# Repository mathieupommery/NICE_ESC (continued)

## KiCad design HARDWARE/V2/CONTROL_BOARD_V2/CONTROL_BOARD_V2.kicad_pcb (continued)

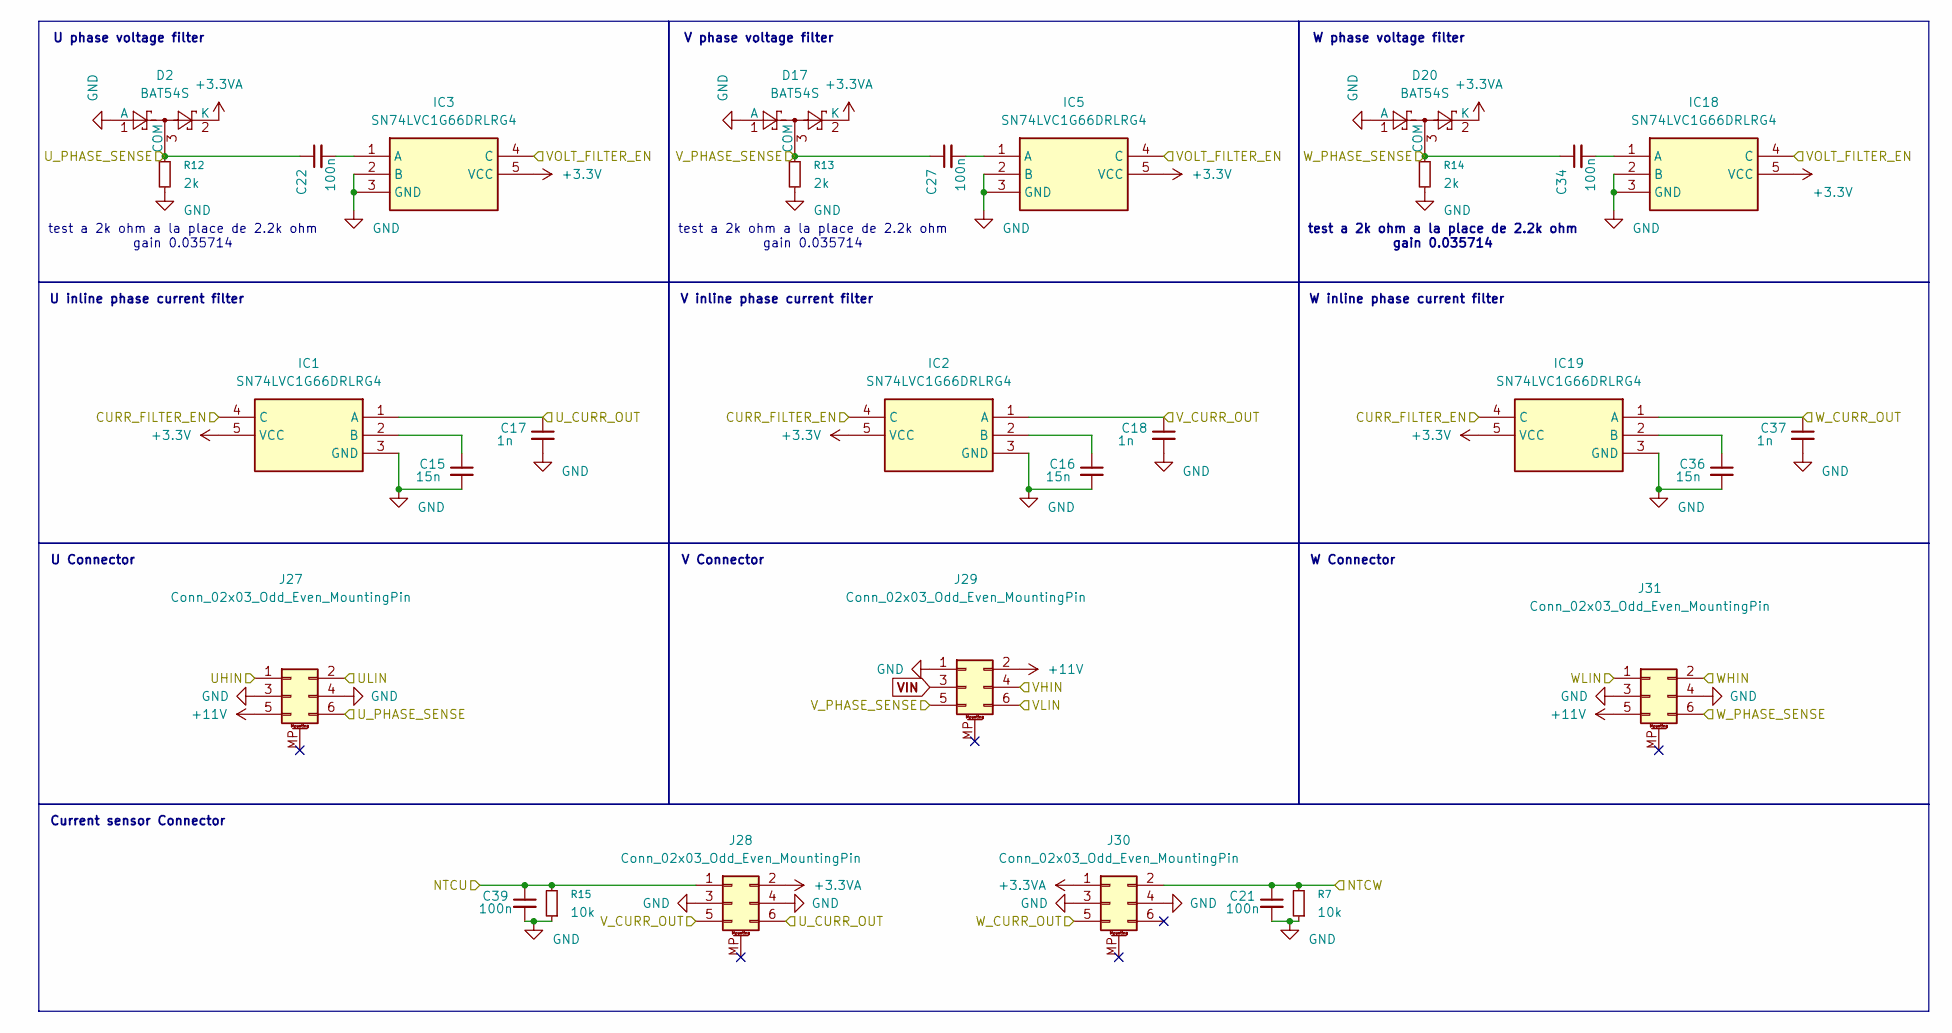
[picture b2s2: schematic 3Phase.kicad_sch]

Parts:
C15, C16, C36: 15n; C_0402_1005Metric
C17, C18, C37: 1n; C_0402_1005Metric
C21, C22, C27, C34, C39: 100n; C_0402_1005Metric
D2, D17, D20: BAT54S; SOT-23
IC1, IC2, IC3, IC5, IC18, IC19: SN74LVC1G66DRLRG4; SOTFL50P160X60-5N; Manufacturer_Part_Number SN74LVC1G66DRLRG4; Mouser Part Number 595-SN74LVC1G66DRG4
J27, J28, J29, J30, J31: Conn_02x03_Odd_Even_MountingPin; 2x3_pinheader
R7, R15: 10k; R_0402_1005Metric
R12, R13, R14: 2k; R_0402_1005Metric

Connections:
+3.3V: IC1.5 (VCC), IC2.5 (VCC), IC3.5 (VCC), IC5.5 (VCC), IC18.5 (VCC), IC19.5 (VCC); also elsewhere on the board
+3.3VA: D2.2 (K), D17.2 (K), D20.2 (K), J28.2, J30.1; also elsewhere on the board
+11V: J27.5, J29.2, J31.5; also elsewhere on the board
/3Phase_Conn_Filtering/UHIN: J27.1; also elsewhere on the board
/3Phase_Conn_Filtering/ULIN: J27.2; also elsewhere on the board
/3Phase_Conn_Filtering/VHIN: J29.4; also elsewhere on the board
/3Phase_Conn_Filtering/VLIN: J29.6; also elsewhere on the board
/3Phase_Conn_Filtering/WHIN: J31.2; also elsewhere on the board
/3Phase_Conn_Filtering/WLIN: J31.1; also elsewhere on the board
/ADC1_IN1: C17.1, IC1.1 (A), J28.6; also elsewhere on the board
/ADC1_IN2: C18.1, IC2.1 (A), J28.5; also elsewhere on the board
/ADC1_IN3: C37.1, IC19.1 (A), J30.5; also elsewhere on the board
/ADC1_IN11: C39.1, J28.1, R15.2; also elsewhere on the board
/ADC1_IN12: C21.1, J30.2, R7.2; also elsewhere on the board
/ADC2_IN3: C22.1, D2.3 (COM), J27.6, R12.1; also elsewhere on the board
/ADC2_IN4: C27.1, D17.3 (COM), J29.5, R13.1; also elsewhere on the board
/ADC2_IN5: C34.1, D20.3 (COM), J31.6, R14.1; also elsewhere on the board
/CURR_FILTER_EN: IC1.4 (C), IC2.4 (C), IC19.4 (C); also elsewhere on the board
/VOLT_FILTER_EN: IC3.4 (C), IC5.4 (C), IC18.4 (C); also elsewhere on the board
GND: C15.2, C16.2, C17.2, C18.2, C21.2, C36.2, C37.2, C39.2, D2.1 (A), D17.1 (A), D20.1 (A), IC1.3 (GND), IC2.3 (GND), IC3.2 (B), IC3.3 (GND), IC5.2 (B), IC5.3 (GND), IC18.2 (B), IC18.3 (GND), IC19.3 (GND), J27.3, J27.4, J28.3, J28.4, J29.1, J30.3, J30.4, J31.3, J31.4, R7.1, R12.2, R13.2, R14.2, R15.1; also elsewhere on the board
unnamed: C15.1, IC1.2 (B)
unnamed: C16.1, IC2.2 (B)
unnamed: C22.2, IC3.1 (A)
unnamed: C27.2, IC5.1 (A)
unnamed: C34.2, IC18.1 (A)
unnamed: C36.1, IC19.2 (B)
VIN: J29.3; also elsewhere on the board

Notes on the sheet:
W phase voltage filter
test a 2k ohm a la place de 2.2k ohm gain 0.035714
U Connector
U phase voltage filter
W inline phase current filter
W Connector
Current sensor Connector
V phase voltage filter
U inline phase current filter
V Connector
V inline phase current filter

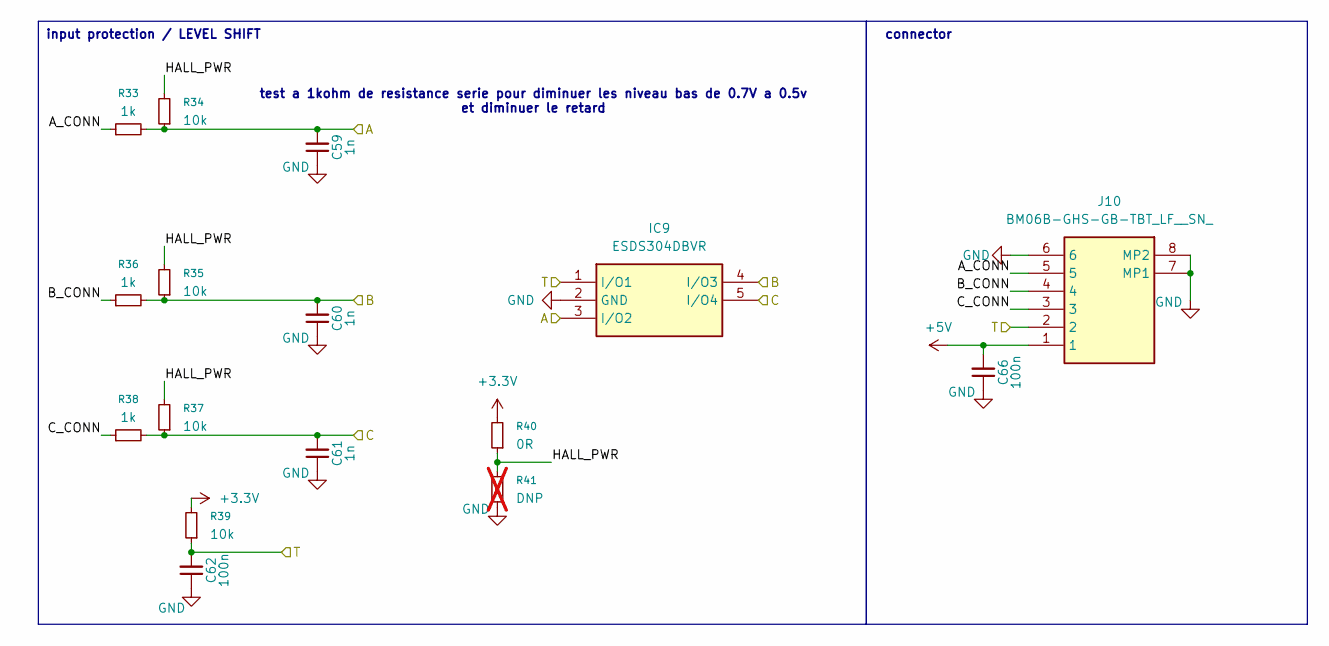
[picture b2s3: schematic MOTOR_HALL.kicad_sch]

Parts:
C59, C60, C61: 1n; C_0402_1005Metric
C62, C66: 100n; C_0402_1005Metric
IC9: ESDS304DBVR; SOT95P280X145-5N; Manufacturer_Part_Number ESDS304DBVR; Mouser Part Number 595-ESDS304DBVR
J10: BM06B-GHS-GB-TBT_LF__SN_; BM06BGHSGBTBTLFSN; Manufacturer_Part_Number BM06B-GHS-GB-TBT(LF)(SN); Mouser Part Number 306-6BGHSGBTBTLN
R33, R36, R38: 1k; R_0402_1005Metric
R34, R35, R37, R39: 10k; R_0402_1005Metric
R40: 0R; R_0402_1005Metric
R41: DNP; R_0402_1005Metric; not fitted

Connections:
+3.3V: R39.2, R40.2; also elsewhere on the board
+5V: C66.2, J10.1; also elsewhere on the board
/ADC1_IN14: C62.2, IC9.1 (I/O1), J10.2, R39.1; also elsewhere on the board
/MOTOR_HALL/A_CONN: J10.5, R33.1
/MOTOR_HALL/B_CONN: J10.4, R36.1
/MOTOR_HALL/C_CONN: J10.3, R38.1
/MOTOR_HALL/HALL_PWR: R34.2, R35.2, R37.2, R40.1, R41.2
/TIM3_CH1: C59.2, IC9.3 (I/O2), R33.2, R34.1; also elsewhere on the board
/TIM3_CH2: C60.2, IC9.4 (I/O3), R35.1, R36.2; also elsewhere on the board
/TIM3_CH3: C61.2, IC9.5 (I/O4), R37.1, R38.2; also elsewhere on the board
GND: C59.1, C60.1, C61.1, C62.1, C66.1, IC9.2 (GND), J10.6, J10.7 (MP1), J10.8 (MP2), R41.1; also elsewhere on the board

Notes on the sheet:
test a 1kohm de resistance serie pour diminuer les niveau bas de 0.7V a 0.5v et diminuer le retard
connector
input protection / LEVEL SHIFT

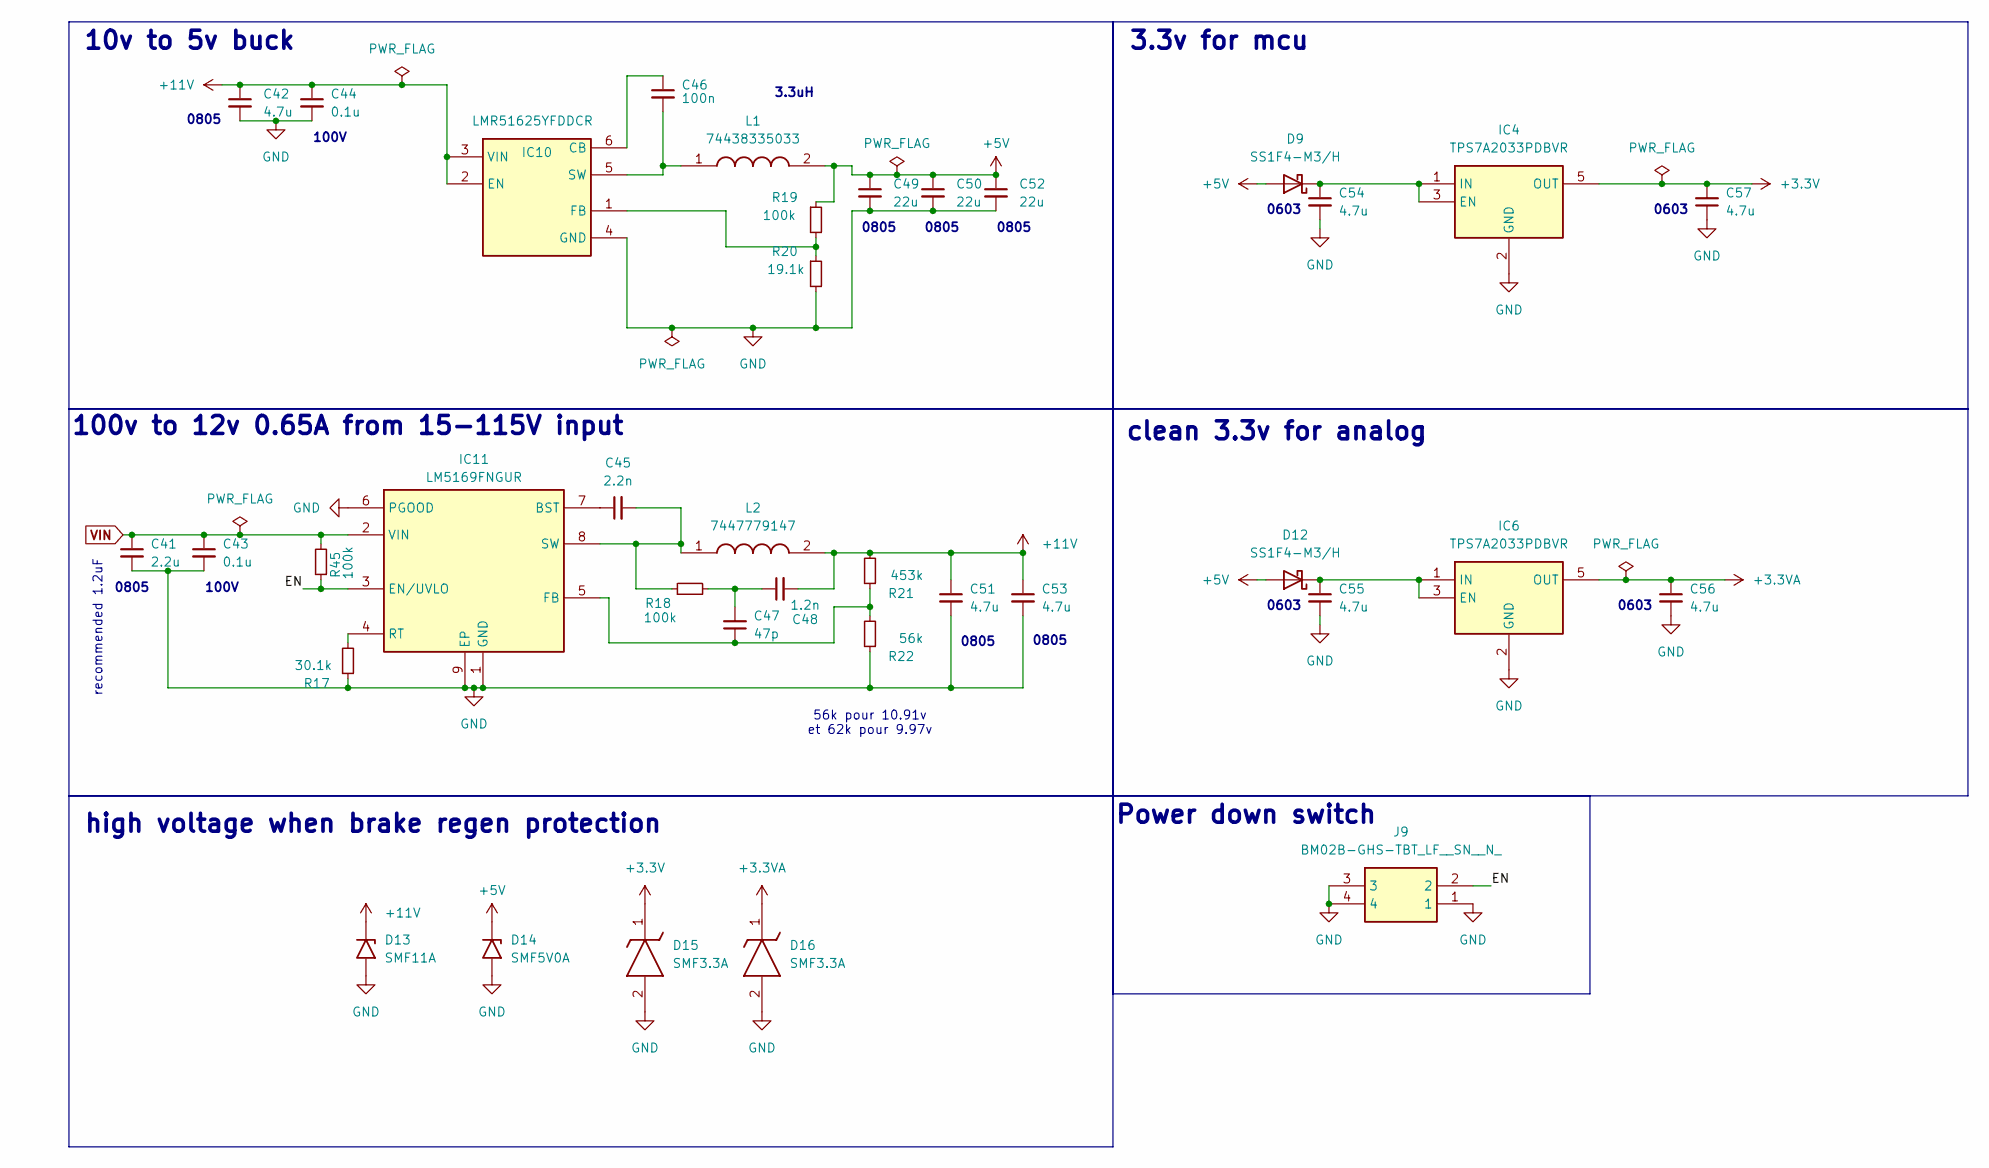
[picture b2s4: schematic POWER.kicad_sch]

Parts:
C41: 2.2u; C_0805_2012Metric
C42, C51, C53: 4.7u; C_0805_2012Metric
C43, C44: 0.1u; C_0402_1005Metric
C45: 2.2n; C_0402_1005Metric
C46: 100n; C_0402_1005Metric
C47: 47p; C_0402_1005Metric
C48: 1.2n; C_0402_1005Metric
C49, C50, C52: 22u; C_0805_2012Metric
C54, C55, C56, C57: 4.7u; C_0603_1608Metric; Manufacturer_Part_Number 885012105012; Mouser Part Number 710-885012105012
D9, D12: SS1F4-M3/H; D_SMF
D13: SMF11A; D_SMF
D14: SMF5V0A; D_SMF
D15, D16: SMF3.3A; SODFL3718X130N; Manufacturer_Part_Number SMF3.3A
IC4, IC6: TPS7A2033PDBVR; SOT95P280X145-5N; Manufacturer_Part_Number TPS7A2033PDBVR; Mouser Part Number 595-TPS7A2033PDBVR
IC10: LMR51625YFDDCR; SOT95P280X110-6N; Manufacturer_Part_Number LMR51625YFDDCR; Mouser Part Number 595-LMR51625YFDDCR
IC11: LM5169FNGUR; SON80P400X400X80-9N-D; Manufacturer_Part_Number LM5169FNGUR; Mouser Part Number 595-LM5169FNGUR
J9: BM02B-GHS-TBT_LF__SN__N_; BM02BGHSTBTLFSNN; Manufacturer_Part_Number BM02B-GHS-TBT(LF)(SN)(N)
L1: 74438335033; INDC3030X150N; Manufacturer_Part_Number 74438335033; Mouser Part Number 710-74438335033
L2: 7447779147; INDPM7473X320N; Manufacturer_Part_Number 7447779147; Mouser Part Number 710-7447779147
R17: 30.1k; R_0402_1005Metric
R18, R19, R45: 100k; R_0402_1005Metric
R20: 19.1k; R_0402_1005Metric
R21: 453k; R_0402_1005Metric
R22: 56k; R_0402_1005Metric

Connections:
+3.3V: C57.2, D15.1 (K), IC4.5 (OUT); also elsewhere on the board
+3.3VA: C56.1, D16.1 (K), IC6.5 (OUT); also elsewhere on the board
+5V: C49.1, C50.1, C52.1, D9.2 (A), D12.2 (A), D14.1 (A1), L1.2, R19.1; also elsewhere on the board
+11V: C42.1, C44.1, C48.2, C51.1, C53.1, D13.1 (A1), IC10.2 (EN), IC10.3 (VIN), L2.2, R21.2; also elsewhere on the board
/POWER/EN: IC11.3 (EN/UVLO), J9.2, R45.1
GND: C41.2, C42.2, C43.2, C44.2, C49.2, C50.2, C51.2, C52.2, C53.2, C54.2, C55.2, C56.2, C57.1, D13.2 (A2), D14.2 (A2), D15.2 (A), D16.2 (A), IC4.2 (GND), IC6.2 (GND), IC10.4 (GND), IC11.1 (GND), IC11.6 (PGOOD), IC11.9 (EP), J9.1, J9.3, J9.4, R17.1, R20.2, R22.1; also elsewhere on the board
unnamed: C47.2, C48.1, R18.2
unnamed: C54.1, D9.1 (K), IC4.1 (IN), IC4.3 (EN)
unnamed: C55.1, D12.1 (K), IC6.1 (IN), IC6.3 (EN)
unnamed: C46.1, IC10.6 (CB)
unnamed: IC10.1 (FB), R19.2, R20.1
unnamed: C46.2, IC10.5 (SW), L1.1
unnamed: C45.1, IC11.7 (BST)
unnamed: C47.1, IC11.5 (FB), R21.1, R22.2
unnamed: IC11.4 (RT), R17.2
unnamed: C45.2, IC11.8 (SW), L2.1, R18.1
VIN: C41.1, C43.1, IC11.2 (VIN), R45.2; also elsewhere on the board

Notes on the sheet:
recommended 1.2uF
0805
0603
clean 3.3v for analog
100V
10v to 5v buck
high voltage when brake regen protection
56k pour 10.91v et 62k pour 9.97v
100v to 12v 0.65A from 15-115V input
Power down switch
3.3uH
3.3v for mcu

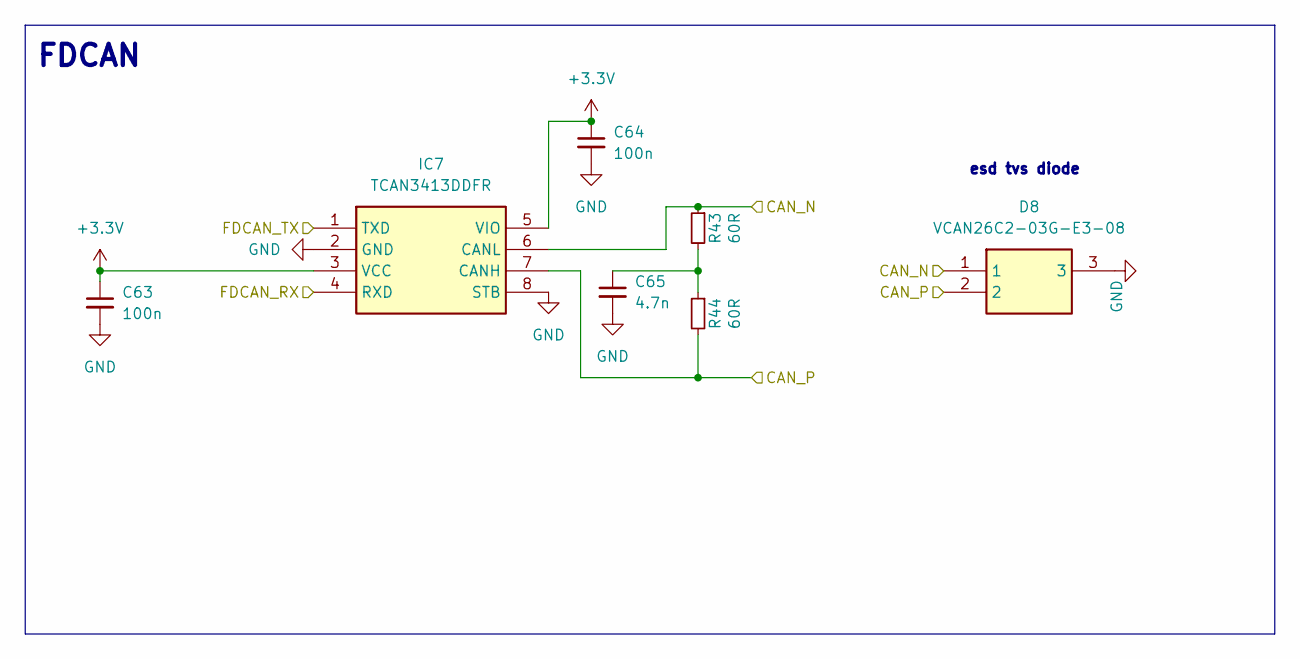
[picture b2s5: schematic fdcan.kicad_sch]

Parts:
C63, C64: 100n; C_0402_1005Metric; Manufacturer_Part_Number 885012104005; Mouser Part Number 710-885012104005
C65: 4.7n; C_0402_1005Metric; Manufacturer_Part_Number 885012104008; Mouser Part Number 710-885012104008
D8: VCAN26C2-03G-E3-08; SOT65P230X110-3N; Manufacturer_Part_Number VCAN26C2-03G-E3-08; Mouser Part Number 72-VCAN26C2-03G-E308
IC7: TCAN3413DDFR; SOT65P280X110-8N; Manufacturer_Part_Number TCAN3413DDFR; Mouser Part Number 595-TCAN3413DDFR
R43, R44: 60R; R_0402_1005Metric; Manufacturer_Part_Number ERJ-1GNF59R0C; Mouser Part Number 667-ERJ-1GNF59R0C

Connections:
+3.3V: C63.1, C64.1, IC7.3 (VCC), IC7.5 (VIO); also elsewhere on the board
/CAN_N: D8.1, IC7.6 (CANL), R43.1; also elsewhere on the board
/CAN_P: D8.2, IC7.7 (CANH), R44.2; also elsewhere on the board
/FDCAN1_RX: IC7.4 (RXD); also elsewhere on the board
/FDCAN1_TX: IC7.1 (TXD); also elsewhere on the board
GND: C63.2, C64.2, C65.2, D8.3, IC7.2 (GND), IC7.8 (STB); also elsewhere on the board
unnamed: C65.1, R43.2, R44.1

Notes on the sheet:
FDCAN
esd tvs diode

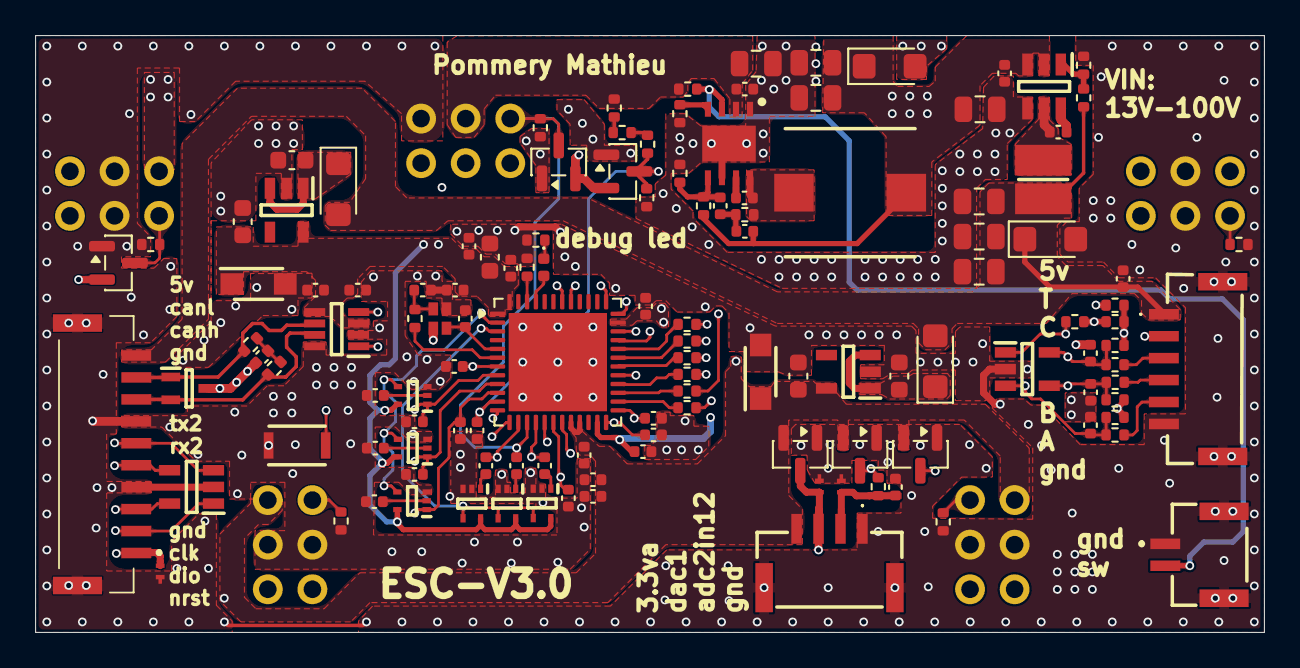
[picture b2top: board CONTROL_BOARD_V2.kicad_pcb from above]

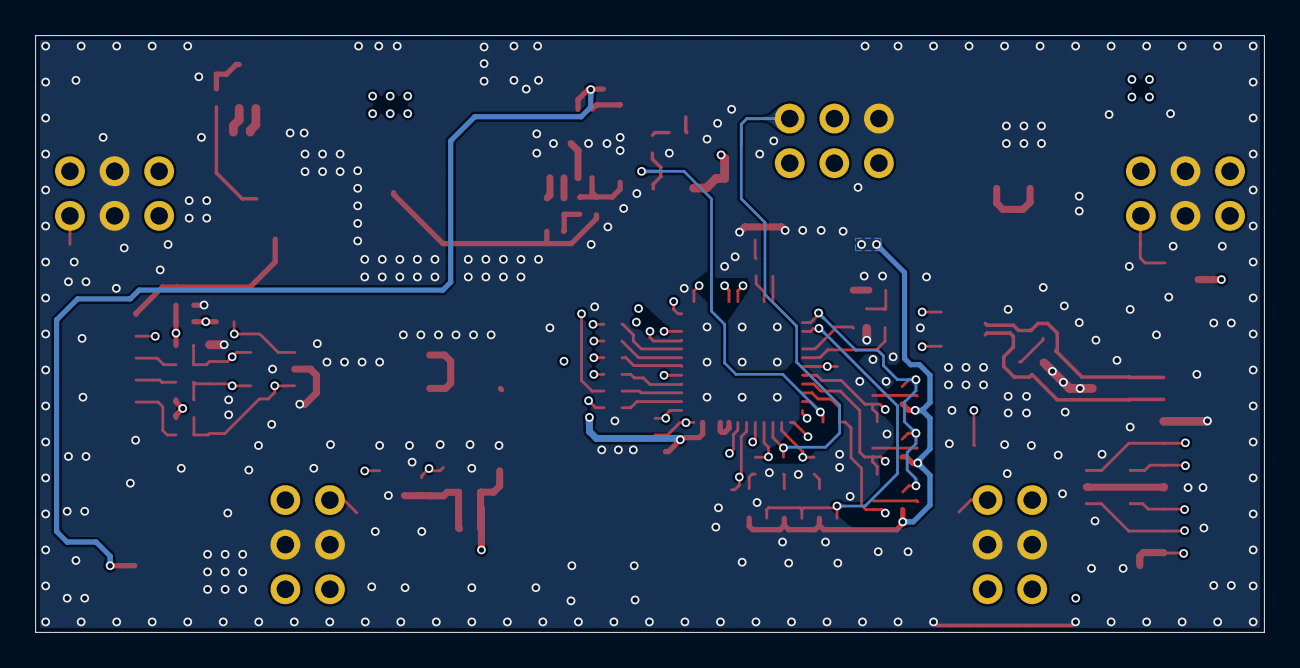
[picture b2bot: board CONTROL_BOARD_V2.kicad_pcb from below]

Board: 4 copper layers, 70.0 x 34.0 mm, 131 parts (5 on the bottom side), 75 nets.
